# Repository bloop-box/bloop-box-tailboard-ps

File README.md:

# Bloop Box Tailboard with Power Supply

## THIS IS NO LONGER MAINTAINED AND THEREFORE ARCHIVED! 

[Documentation](https://bloop-box.github.io/bloop-box-tailboard)

The board is designed using KiCAD 6 with production and assembly by JLCPCB in mind. All parts are selected to be
available from JLCPCB. At the time of writing as many parts as possible are used from their basic library.

- two power inputs
  - 5.5x2.1mm barrel-jack
  - USB-C
- Can handle 5V to 28V inputs
- Can deliver 5V with up to 3A to the mainboard (assuming it gets enough power)
- Additional circuitry to prevent damage in case two power supplies are connected
- Two buttons connected to the Raspberry Pi, per default used for volume control
- Three LEDs 
  - One to show status of power supply
  - Two can be remote-controlled by Raspberry Pi through the Mainboard

If you just need the 5V USB-C input and don't want the active circuitry you can use the [Tailboard Light](https://github.com/bloop-box/bloop-box-tailboard-light).

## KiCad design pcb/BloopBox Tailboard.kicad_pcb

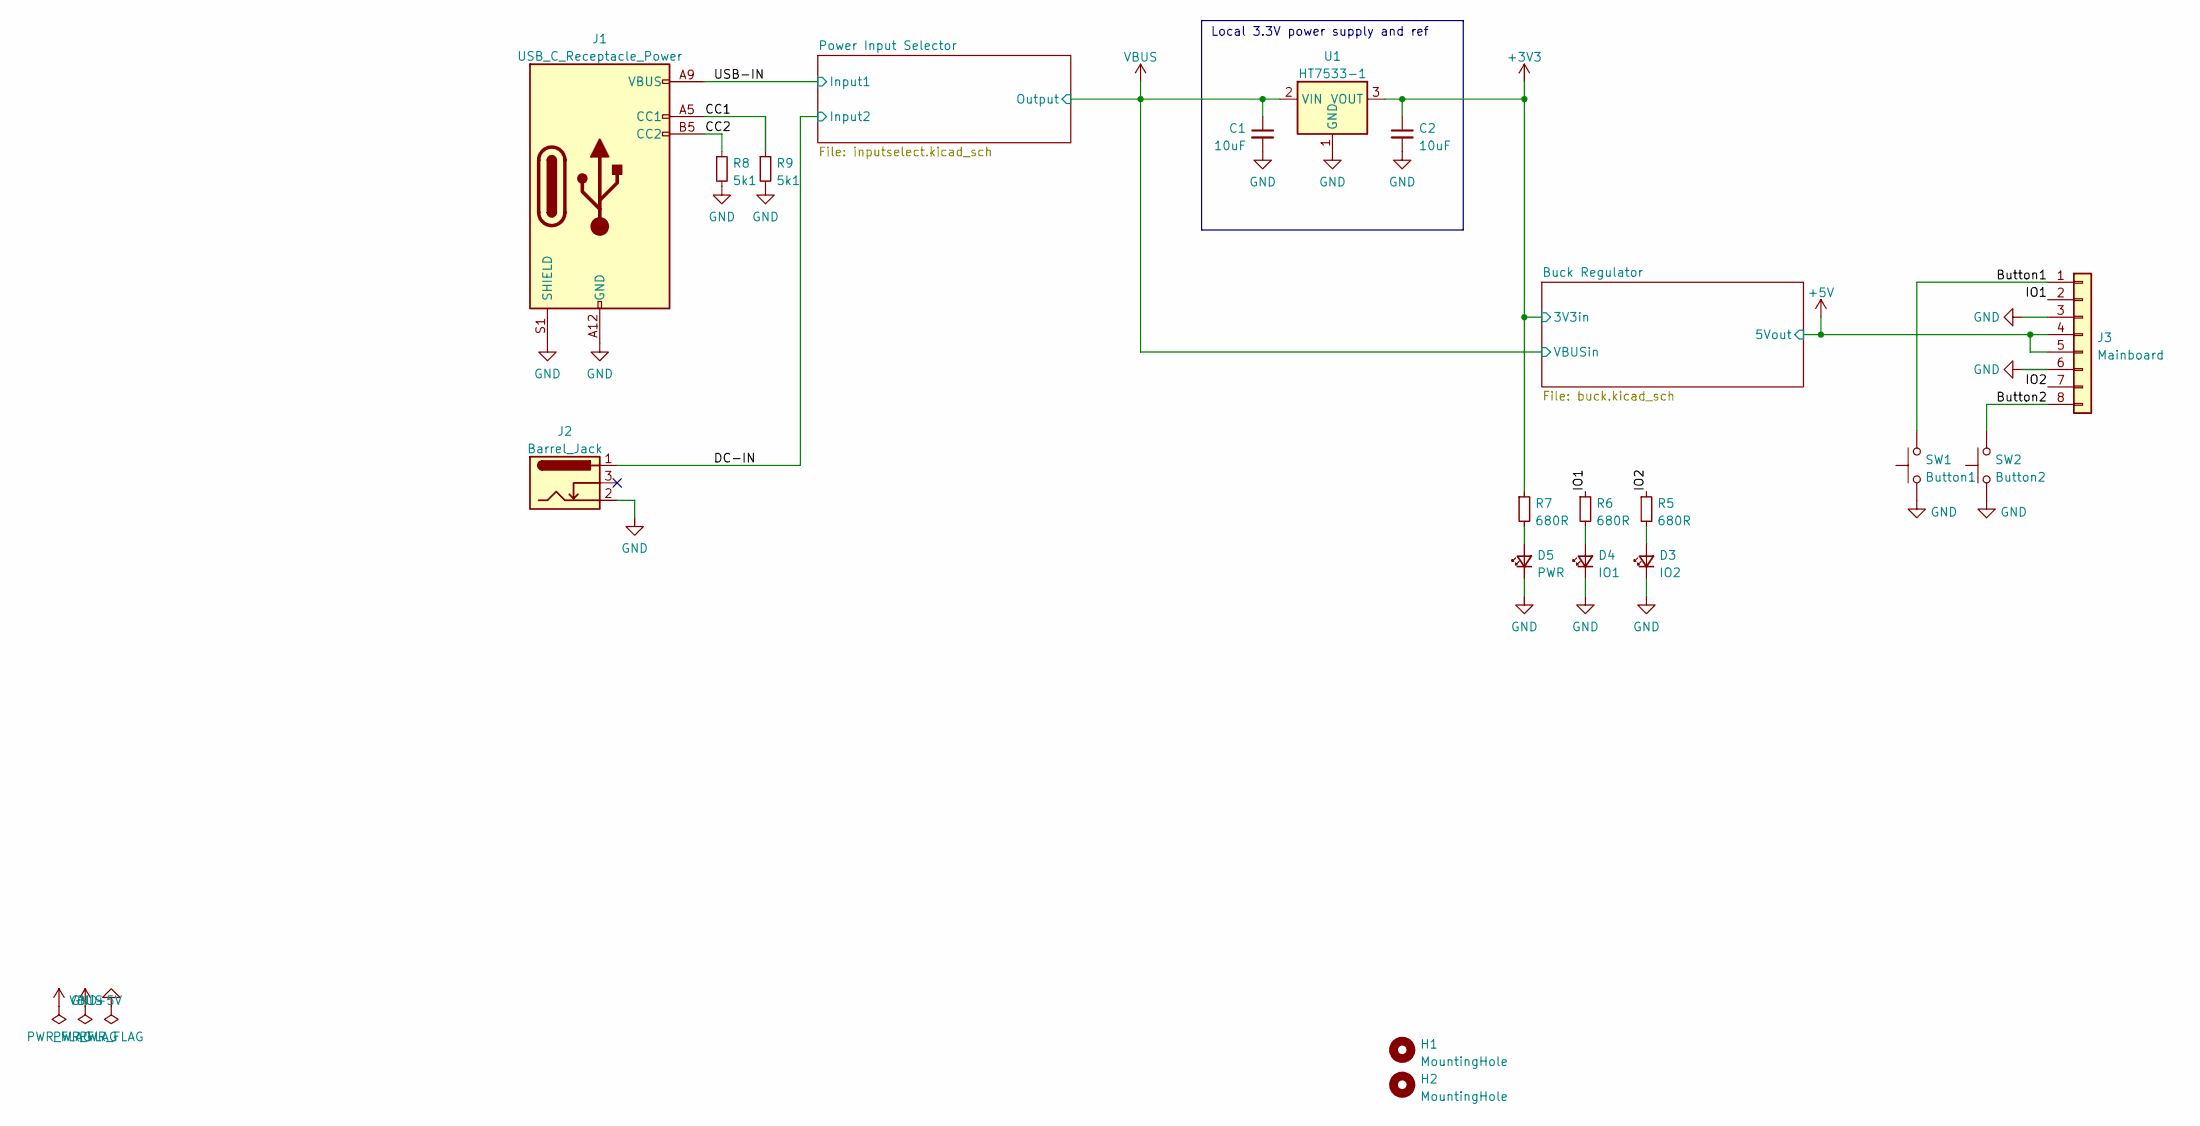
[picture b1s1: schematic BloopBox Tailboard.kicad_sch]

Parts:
C1: 10uF; C_0805_2012Metric; LCSC C440198
C2: 10uF; C_0402_1005Metric; LCSC C15525
D3: IO2; LED_0603_1608Metric; LCSC C72038
D4: IO1; LED_0603_1608Metric; LCSC C72038
D5: PWR; LED_0603_1608Metric; LCSC C72038
H1, H2: MountingHole; MountingHole_3.2mm_M3_Pad
J1: USB_C_Receptacle_Power; GCT_USB4125-GF-A_REVA2; LCSC C283540
J2: Barrel_Jack; BarrelJack_Horizontal
J3: Mainboard; JST_PH_S8B-PH-K_1x08_P2.00mm_Horizontal; LCSC C14531
R5, R6, R7: 680R; R_0402_1005Metric; LCSC C25130
R8, R9: 5k1; R_0402_1005Metric; LCSC C25905
SW1: Button1; SW_Tactile_SPST_Angled_PTS645Vx83-2LFS; LCSC C338650
SW2: Button2; SW_Tactile_SPST_Angled_PTS645Vx83-2LFS; LCSC C338650
U1: HT7533-1; SOT-89-3; LCSC C14289

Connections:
+3V3: C2.1, R7.1, U1.3 (VOUT); also elsewhere on the board
+5V: J3.4, J3.5; also elsewhere on the board
/Button1: J3.1, SW1.2
/Button2: J3.8, SW2.2
/CC1: J1.A5 (CC1), R9.1
/CC2: J1.B5 (CC2), R8.1
/DC-IN: J2.1; also elsewhere on the board
/IO1: J3.2, R6.1
/IO2: J3.7, R5.1
/USB-IN: J1.A9 (VBUS), J1.B9 (VBUS); also elsewhere on the board
GND: C1.2, C2.2, D3.1 (K), D4.1 (K), D5.1 (K), J1.A12 (GND), J1.B12 (GND), J1.S1 (SHIELD), J2.2, J3.3, J3.6, R8.2, R9.2, SW1.1, SW2.1, U1.1 (GND); also elsewhere on the board
unnamed: D3.2 (A), R5.2
unnamed: D4.2 (A), R6.2
unnamed: D5.2 (A), R7.2
VBUS: C1.1, U1.2 (VIN); also elsewhere on the board

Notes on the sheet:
Local 3.3V power supply and ref

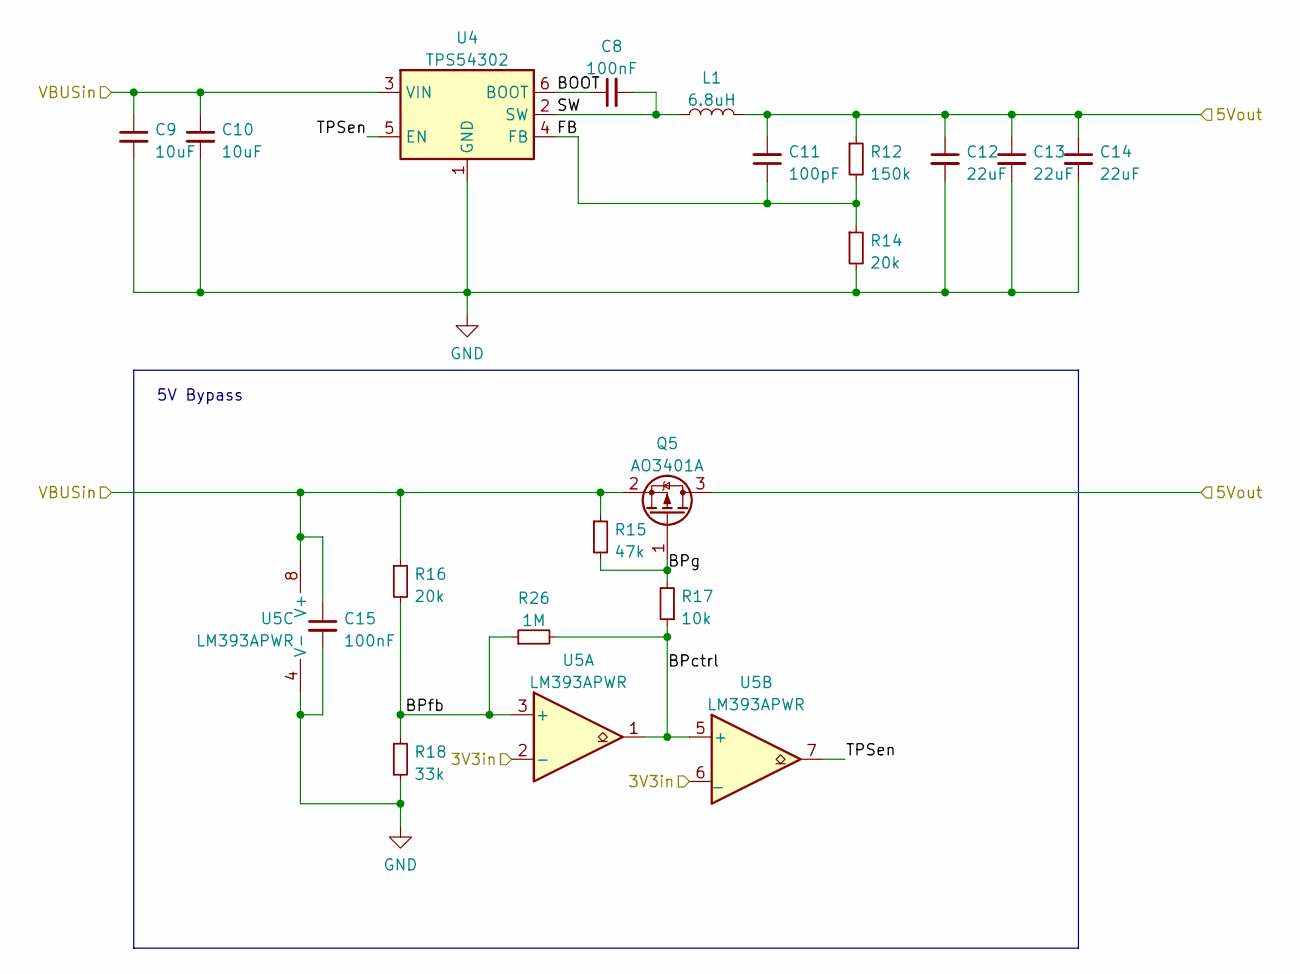
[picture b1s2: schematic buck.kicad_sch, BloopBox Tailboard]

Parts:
C8: 100nF; C_0402_1005Metric; LCSC C1525
C9, C10: 10uF; C_1206_3216Metric; LCSC C13585
C11: 100pF; C_0402_1005Metric; LCSC C1546
C12, C13, C14: 22uF; C_1206_3216Metric; LCSC C5672
C15: 100nF; C_0402_1005Metric; LCSC C307331
L1: 6.8uH; L_Bourns_SRP7028A_7.3x6.6mm; LCSC C400395
Q5: AO3401A; SOT-23; LCSC C15127
R12: 150k; R_0402_1005Metric; LCSC C25755
R14, R16: 20k; R_0402_1005Metric; LCSC C25765
R15: 47k; R_0402_1005Metric; LCSC C25792
R17: 10k; R_0402_1005Metric; LCSC C25744
R18: 33k; R_0402_1005Metric; LCSC C25779
R26: 1M; R_0402_1005Metric; LCSC C26083
U4: TPS54302; SOT-23-6; LCSC C311983
U5: LM393APWR; TSSOP-8_4.4x3mm_P0.65mm; LCSC C527473

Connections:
+3V3: U5.2 (-), U5.6 (_); also elsewhere on the board
+5V: C11.2, C12.1, C13.1, C14.1, L1.2, Q5.3 (D), R12.1; also elsewhere on the board
/Buck Regulator/BOOT: C8.1, U4.6 (BOOT)
/Buck Regulator/BPctrl: R17.1, R26.2, U5.1, U5.5 (+)
/Buck Regulator/BPfb: R16.2, R18.1, R26.1, U5.3 (+)
/Buck Regulator/BPg: Q5.1 (G), R15.2, R17.2
/Buck Regulator/FB: C11.1, R12.2, R14.1, U4.4 (FB)
/Buck Regulator/SW: C8.2, L1.1, U4.2 (SW)
/Buck Regulator/TPSen: U4.5 (EN), U5.7
GND: C9.2, C10.2, C12.2, C13.2, C14.2, C15.2, R14.2, R18.2, U4.1 (GND), U5.4 (V-); also elsewhere on the board
VBUS: C9.1, C10.1, C15.1, Q5.2 (S), R15.1, R16.1, U4.3 (VIN), U5.8 (V+); also elsewhere on the board

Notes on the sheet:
5V Bypass

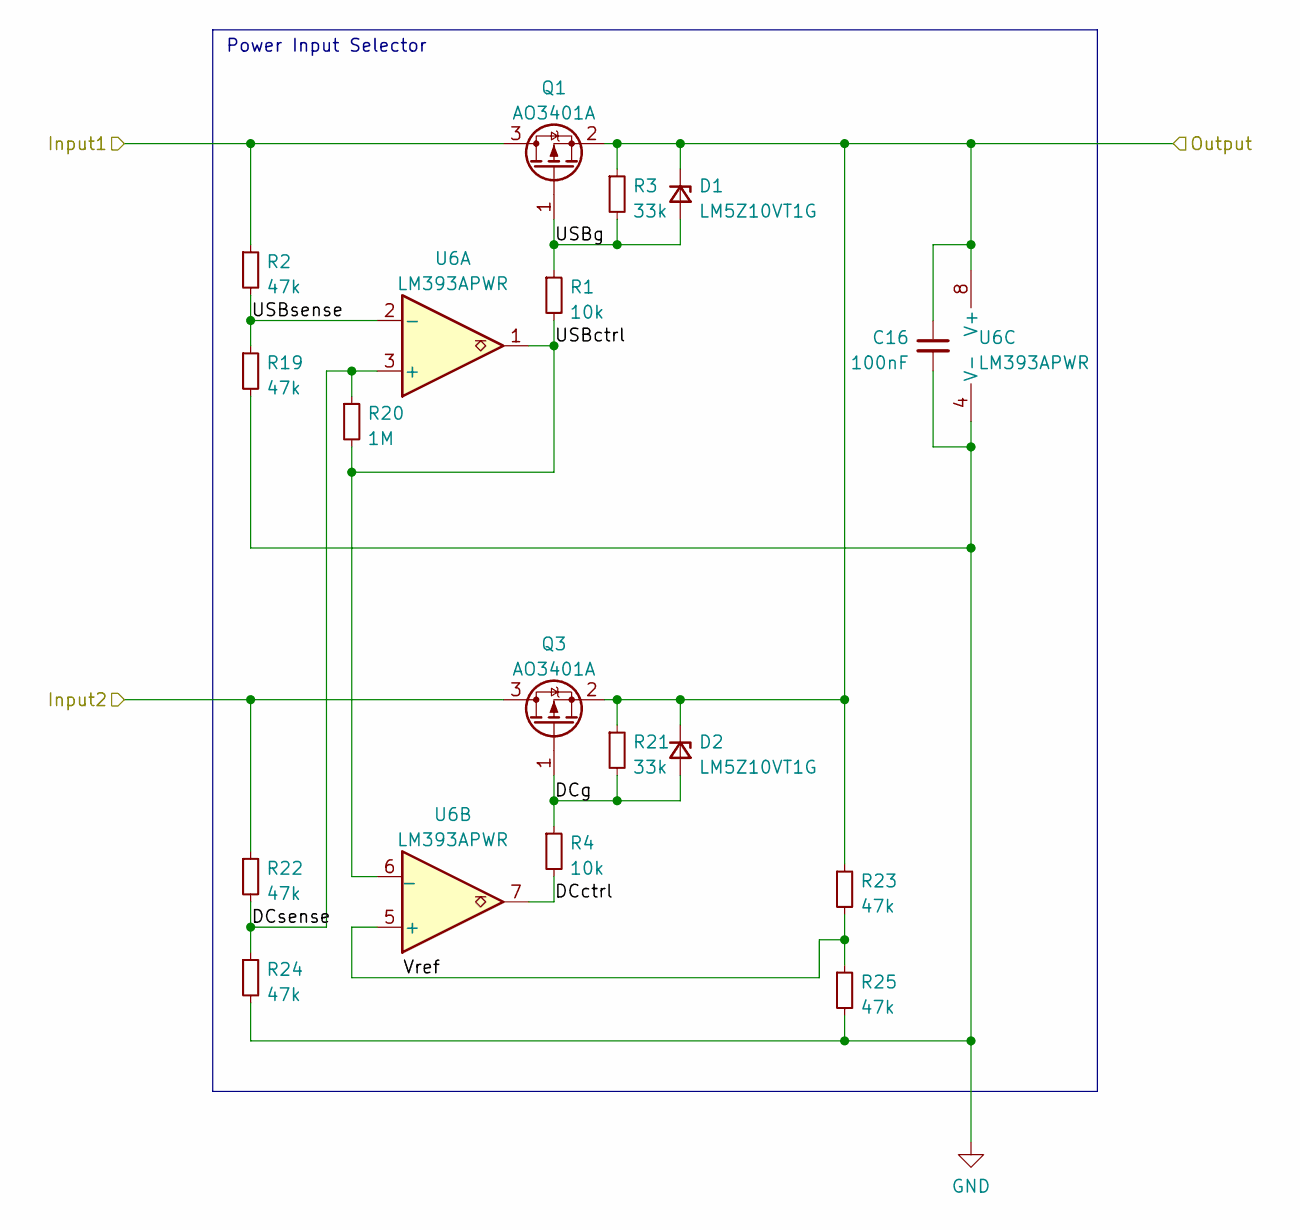
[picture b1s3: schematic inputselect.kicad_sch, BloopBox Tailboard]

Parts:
C16: 100nF; C_0402_1005Metric; LCSC C307331
D1, D2: LM5Z10VT1G; D_SOD-523; LCSC C525398
Q1, Q3: AO3401A; SOT-23; LCSC C15127
R1, R4: 10k; R_0402_1005Metric; LCSC C25744
R2, R19, R22, R23, R24, R25: 47k; R_0402_1005Metric; LCSC C25792
R3, R21: 33k; R_0402_1005Metric; LCSC C25779
R20: 1M; R_0402_1005Metric; LCSC C26083
U6: LM393APWR; TSSOP-8_4.4x3mm_P0.65mm; LCSC C527473

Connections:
/DC-IN: Q3.3 (D), R22.1; also elsewhere on the board
/Power Input Selector/DCctrl: R4.2, U6.7
/Power Input Selector/DCg: D2.2 (A), Q3.1 (G), R4.1, R21.2
/Power Input Selector/DCsense: R20.1, R22.2, R24.1, U6.3 (+)
/Power Input Selector/USBctrl: R1.2, R20.2, U6.1, U6.6 (_)
/Power Input Selector/USBg: D1.2 (A), Q1.1 (G), R1.1, R3.2
/Power Input Selector/USBsense: R2.2, R19.1, U6.2 (-)
/Power Input Selector/Vref: R23.2, R25.1, U6.5 (+)
/USB-IN: Q1.3 (D), R2.1; also elsewhere on the board
GND: C16.2, R19.2, R24.2, R25.2, U6.4 (V-); also elsewhere on the board
VBUS: C16.1, D1.1 (K), D2.1 (K), Q1.2 (S), Q3.2 (S), R3.1, R21.1, R23.1, U6.8 (V+); also elsewhere on the board

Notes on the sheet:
Power Input Selector

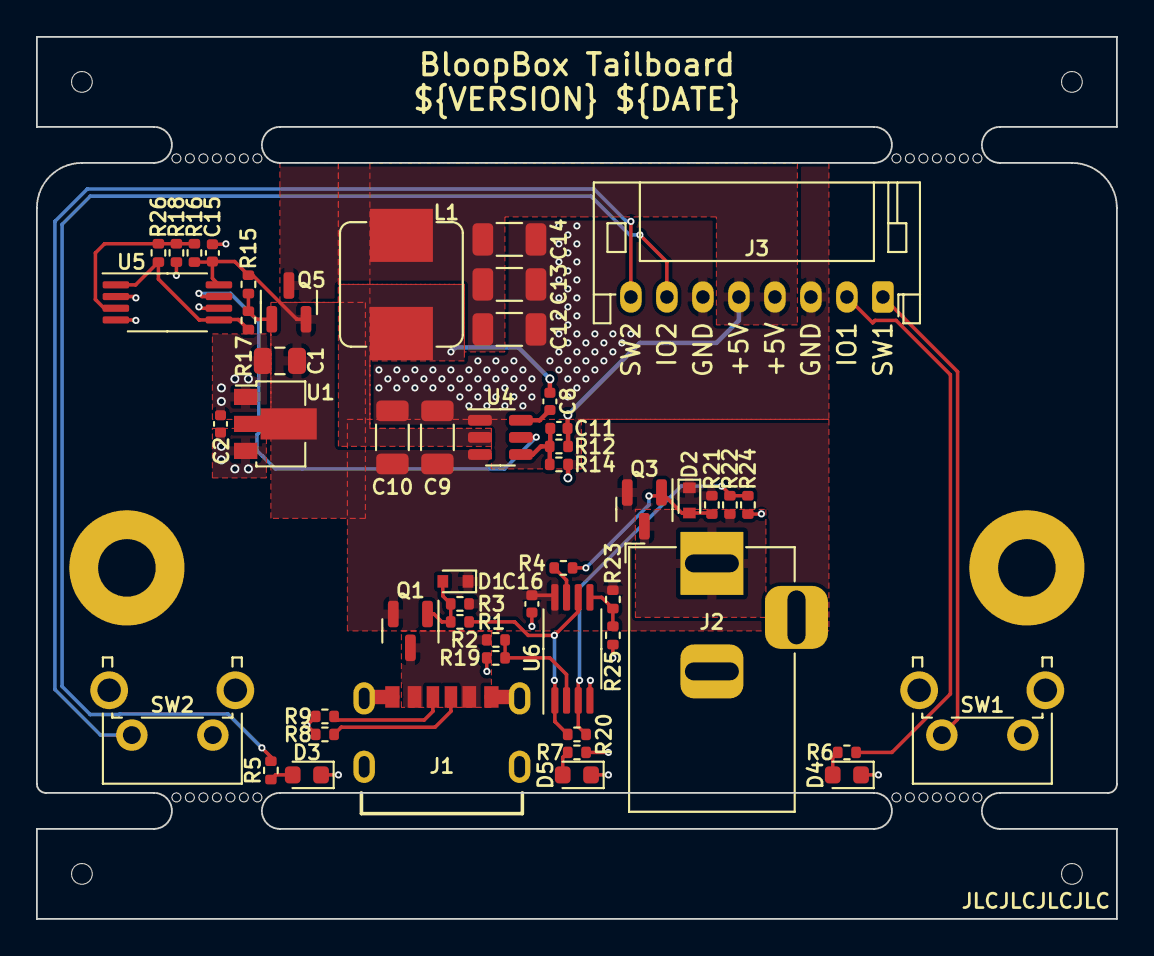
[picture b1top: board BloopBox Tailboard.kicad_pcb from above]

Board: 4 copper layers, 60.0 x 49.0 mm, 58 parts (0 on the bottom side), 29 nets.

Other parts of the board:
mouse-bite-2mm-slot, mouse-bite-2mm-slot#2, mouse-bite-2mm-slot#3, mouse-bite-2mm-slot#4: VAL**; mouse-bite-2x5mm-slot-onesided

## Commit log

2022-12-02 ci: add basic kibot workflow for mainboard
2022-12-02 ci: pass config-file to base workflow
2022-12-02 ci: add remaining boards to kibot
2022-12-02 docs: add CERN OHL-P license
2022-12-02 ci: update kibot.yml settings
2022-12-02 docs: add github status badges to README.md
2022-12-02 chore: remove .kicad_prl files from git
2022-12-02 docs: fill README with useful information
2022-12-03 docs: add details about NFC reader
2022-12-03 ci: add doc generation to GH pages repository
2022-12-03 ci: add missing type to kibot.yml
2022-12-03 ci: pass DOCS_DEPLOY_KEY secret down to reusable workflow
2022-12-03 ci: fix secret passing
2022-12-03 ci: refactor ci workflow
2022-12-03 ci: remove unused needs-dependency
2022-12-03 ci: fix name of input parameter
2022-12-03 ci: fix artifact deployment
2022-12-03 ci: add missing runs-on to deploy step
2022-12-03 ci: fix version of upload-pages-artifact action
2022-12-03 ci: add index.html file for navigate results
2022-12-03 docs: add renders and documentation links to README
2022-12-03 chore: add KiCAD autosave files to .gitignore
2022-12-03 style(Tailboard): rev number +.1
    Forgot to change this...
2022-12-04 feat: split tailboard into standalone repository
2022-12-04 docs: fix image link in README
2022-12-04 feat: add and use versioning variables
2022-12-05 chore: add BSD-2-Clause license for code
2022-12-05 ci: add release-please workflow
2022-12-09 fix!: remove Power Delivery circuitry
    PD circuit was removed because it didn't work as planned in the current version and fixing it would make the board too expensive. The USB-C port is now hardwired to request 5V/3A.
2022-12-09 docs: update README
    Remove Power Deliver and change description of LED functionality
2022-12-11 fix: add missing LCSC part numbers
2022-12-12 docs: add link to Tailboard Light
2022-12-12 chore(main): release 1.0.0
2023-12-02 docs: add archive note
